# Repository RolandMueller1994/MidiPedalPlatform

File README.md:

# MidiPedalPlatform

## Introduction

This project contains a template PCB for guitar effect pedals with MIDI remote functionality. MIDI is implemented using a STM32 F030C8T6 microcontroller.
The PCB is setup to contain four 16mm potentiometers, a SPST on-off-on switch and PCB mounted jack sockets for audio connection. Further connections are the MIDI input and output, an internal switch and an external switch which are all accesible through JST connectors. A programming and debugging connector for the STLINK-V3MINIE is implemented on the PCB.

Following images show a complete pedal build based on this template.

## PCB

The PCB was developed using KiCad and a two layer setup. The KiCad project can be found in [PCB/MidiPedalPlatform](PCB/MidiPedalPlatform) whilst PCB and schematic exports are located in [PCB/Export](PCB/Export).

## Firmware

The MCU firmware is located in the [Firmware](Firmware) directory. It is implemented as STM32CubeIDE project.

The firmware handles switches and MIDI messages. By default, two switches are available: SW and ExtSW. SW is meant to be used as the default internal footswitch and must be a momentary switch. ExtSW can be used to connect an external remote switch and is by default configured to be a latching switch. This can be changed by changing:
```C
bool swLatches[NO_SWITCHES] = { false, true, true }
```
to
```C
bool swLatches[NO_SWITCHES] = { false, false, true }
```
The pedal can be switched on and off via MIDI CC commands. The channel and controller number are stored in the flash memory. Thus, a MIDI learn state and a reset state have been implemented.
To reset both parameters to their default value (channel=0, controller=20), hold the footswitch pressed (SW) while powering on or reseting the MCU till the LED starts blinking. Release the switch afterwards and the LED stops blinking. Default values will then have been written to flash.

MIDI learn is used to set any other channel and controller. This mode can be accessed by holding the footswitch pressed whilst the input jack is not connected. The LED starts blinking once MIDI learn state has been reached. In this mode, the firmware waits for a MIDI CC message and once the first one has been received, it will store the channel and controller of this message in the flash memory. MIDI learn can be aborted by pressing the footswitch again. In either case, MIDI CC received or MIDI learn aborted, the LED stops blinking.
The pedal can be switched on by sending a value greater than 63 to the configured MIDI contoller. Anything lower or equal than 63 will switch off the pedal.

The footswitch can be used in two different ways. 

- Normal activation: Toggles between on and off state
- Keeping the switch pressed whilst the pedal was off: The pedal will turn on as long you keep the switch pressed. Once release, the pedal will turn off.

## Enclosure

The PCB was design to fit into a 1590N1 enclosure. A FreeCAD project including enclosure, PCB, jacks and the switch can be found at [Enclosure/Enclosure.FCStd](Enclosure/Enclosure.FCStd). Renderings of the enclosure can be found below.
Drill templates can be found in [Enclosure/DrillTemplates](Enclosure/DrillTemplates).

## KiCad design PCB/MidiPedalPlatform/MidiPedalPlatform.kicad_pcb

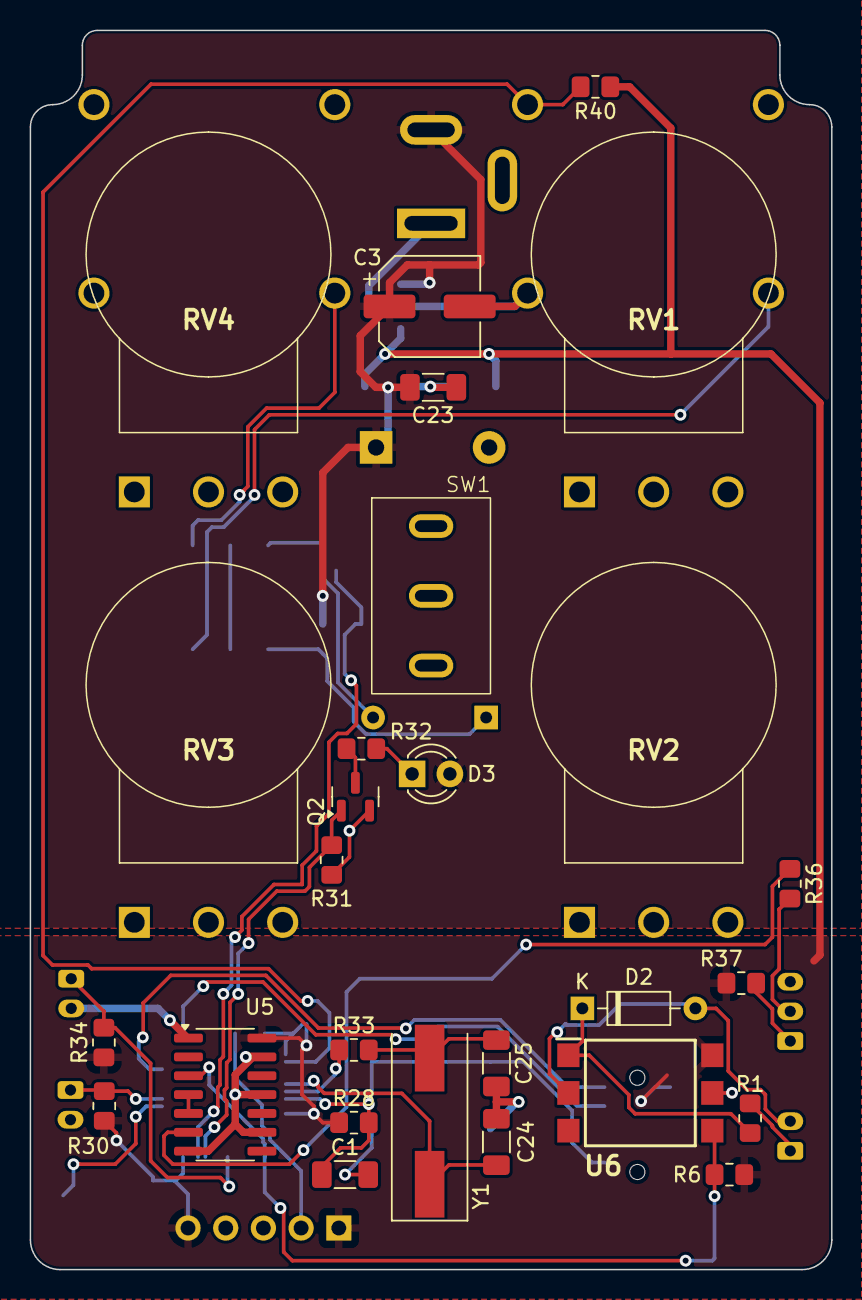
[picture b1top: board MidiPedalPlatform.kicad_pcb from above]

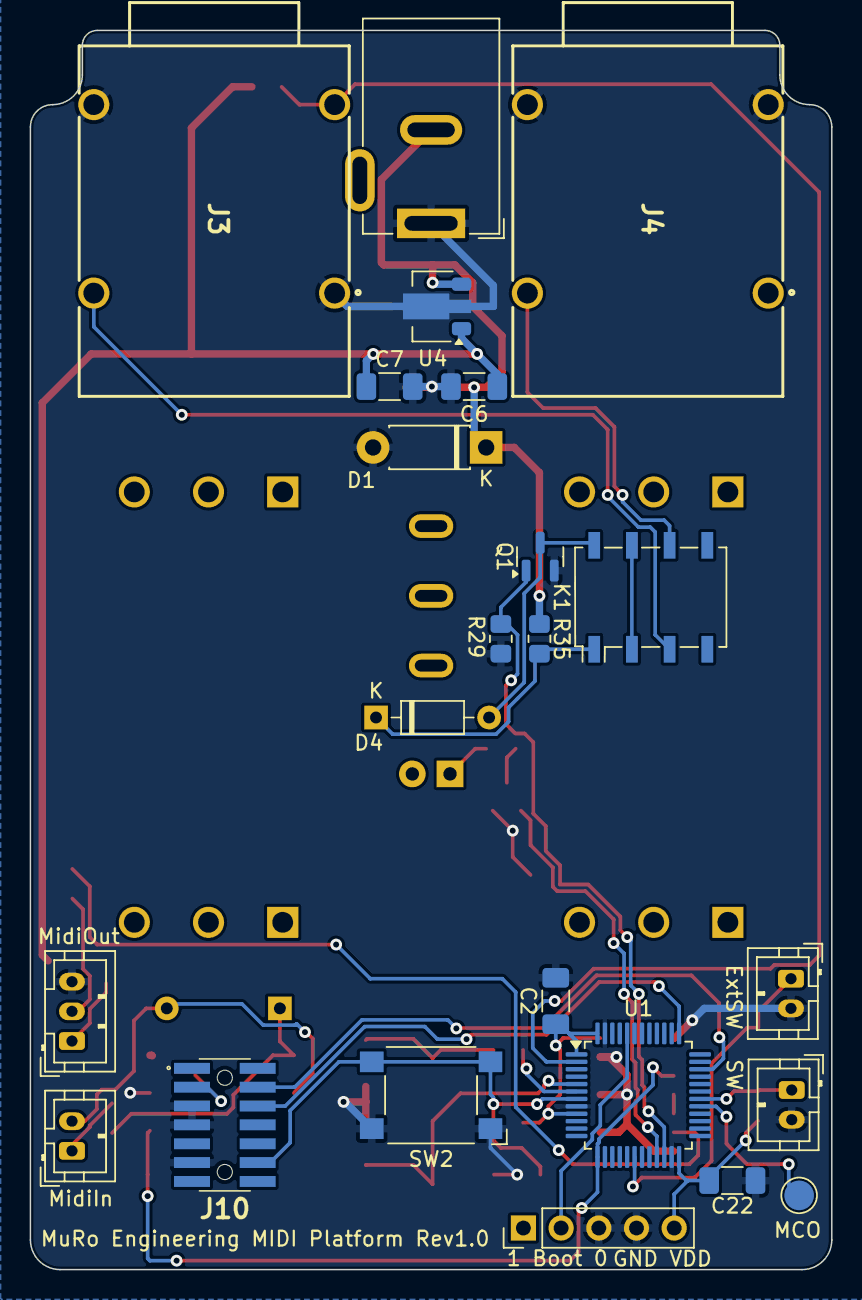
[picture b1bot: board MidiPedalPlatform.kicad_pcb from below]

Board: 2 copper layers, 54.0 x 83.5 mm, 50 parts (23 on the bottom side), 31 nets.

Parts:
C1, C2, C7, C22, C23: 100n; C_1206_3216Metric_Pad1.33x1.80mm_HandSolder
C3: 47u; CP_Elec_6.3x5.8
C6: 4u7; C_1206_3216Metric_Pad1.33x1.80mm_HandSolder
C24, C25: 16p; C_1206_3216Metric_Pad1.33x1.80mm_HandSolder
D1: 1N4001; D_DO-41_SOD81_P7.62mm_Horizontal
D2: 1N914; D_DO-35_SOD27_P7.62mm_Horizontal
D3: LED; LED_D3.0mm
D4: 1N4148; D_DO-35_SOD27_P7.62mm_Horizontal
J1: Barrel_Jack_Switch; BarrelJack_GCT_DCJ200-10-A_Horizontal
J2, J5, J8: Conn_01x02; JST_PH_B2B-PH-K_1x02_P2.00mm_Vertical
J3, J4: AudioJack2_Switch; NMJ4HCD2
J6: Conn_01x05; PinHeader_1x05_P2.54mm_Vertical
J9: Conn_01x03; JST_PH_B3B-PH-K_1x03_P2.00mm_Vertical
J10: Conn_02x07_Odd_Even; FTSH-107-XX-YYY-DV-K-A
K1: G6K-2; Relay_DPDT_Omron_G6K-2F
Q1, Q2: 2N7002; SOT-23
R1: 220; R_0805_2012Metric_Pad1.20x1.40mm_HandSolder
R6: 280; R_0805_2012Metric_Pad1.20x1.40mm_HandSolder
R28, R30, R34, R40: 10k; R_0805_2012Metric_Pad1.20x1.40mm_HandSolder
R29, R31: 100k; R_0805_2012Metric_Pad1.20x1.40mm_HandSolder
R32: 1k5; R_0805_2012Metric_Pad1.20x1.40mm_HandSolder
R33: 390; R_0805_2012Metric_Pad1.20x1.40mm_HandSolder
R35: 180; R_0805_2012Metric_Pad1.20x1.40mm_HandSolder
R36: 10; R_0805_2012Metric_Pad1.20x1.40mm_HandSolder
R37: 33; R_0805_2012Metric_Pad1.20x1.40mm_HandSolder
RV1, RV2, RV3, RV4: B100k; RV16AF_Mono
SW1: SW_SPDT; Switch_SPDT
SW2: SW_Push; SW_SPST_Omron_B3FS-100xP
TP_MCO1: TestPoint; TestPoint_Pad_D2.0mm
U1: STM32F030C8Tx; LQFP-48_7x7mm_P0.5mm
U4: L78L33_SOT89; SOT-89-3
U5: 74HC14; SO-14_3.9x8.65mm_P1.27mm
U6: H11L1; H11L1SM
Y1: 8MHz; Crystal_SMD_HC49-SD

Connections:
/ExtSW: J8.1, R34.2, U1.18 (PB0)
/InConn: J3.SN, R40.2, U1.2 (PC13)
/LED: Q2.1 (G), R31.1, U1.21 (PB10)
/MCU/OSC_IN: C24.1, U1.5 (PF0), Y1.1
/MCU/OSC_OUT: R33.1, U1.6 (PF1)
/MCU/SWCLK: J10.6, U1.37 (PA14)
/MCU/SWDIO: J10.4, U1.34 (PA13)
/MCU/boot0: J6.2, U1.44 (BOOT0)
/MCU/nrst: C1.1, J10.12, R28.2, SW2.2, U1.7 (NRST)
/MIDI_TX: R36.1, U5.6
/MidiSig: R6.1, U1.13 (PA3), U5.3, U6.4
/Relay: Q1.1 (G), R29.1, U1.22 (PB11)
/SW: J5.1, R30.2, U1.30 (PA9)
/VDD: C3.1, C23.1, D1.1 (K), D3.2 (A), J1.2, R35.1, U4.3 (IN)
/VDD3V3: C2.1, C6.1, C7.1, C22.1, J6.1, J6.5, J10.3, R6.2, R28.1, R30.1, R34.1, R37.1, R40.1, U1.1 (VDD), U1.9 (VDDA), U1.24 (VDD), U1.48 (VDD), U4.1 (OUT), U5.14 (VCC), U6.6
GND: C1.2, C2.2, C3.2, C6.2, C7.2, C22.2, C23.2, C24.2, C25.2, D1.2 (A), J1.1, J3.S, J3.TN, J4.S, J4.SN, J5.2, J6.3, J6.4, J8.2, J9.3, J10.5, J10.7, J10.11, Q1.2 (S), Q2.2 (S), R29.2, R31.2, SW2.1, U1.8 (VSSA), U1.23 (VSS), U1.47 (VSS), U4.2 (GND), U5.1, U5.7 (GND), U5.9, U5.11, U5.13, U6.5
unnamed: C25.1, R33.2, Y1.2
unnamed: D2.2 (A), J2.2, U6.2
unnamed: D2.1 (K), R1.2, U6.1
unnamed: D3.1 (K), R32.1
unnamed: D4.2 (A), K1.8, Q1.3 (D)
unnamed: D4.1 (K), K1.1, R35.2
unnamed: J2.1, R1.1
unnamed: J3.T, K1.3
unnamed: J4.T, K1.6
unnamed: J9.1, R37.2
unnamed: J9.2, R36.2
unnamed: K1.2, K1.7
unnamed: Q2.3 (D), R32.2
unnamed: TP_MCO1.1, U1.29 (PA8)
unnamed: U5.4, U5.5

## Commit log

2025-02-16 Initial commit including license and gitignore
2025-02-16 Imported firmware with basic hardware configuration. This is a clean STM32 project for the target microcontroller including the IO configuration.
2025-02-16 First version of switch debouncing.
    In this version, momentary switches are properly debounced and their state is traced for falling edge (active low) operation.
    Dual edge debouncing and latching switch operation yet to be implemented.
2025-02-16 Added push and release edge detection and debouncing.
    With this change, lateched switches can be used to trigger the effectOn state by tracking the edges.
2025-02-16 Added long press functionality for momentary switches.
    This feature detects momentary switches been pressed for longer than a certain time (LONG_DELAY). This can be used to temporarily activate the effect as long as the switched is pressed. After release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
2025-02-16 First midi implemenation. This version only works with CC messages.
2025-02-16 Switched UART to UARTEx functions to use ReceiveToIdle functions.
    MIDI packages are either two or three bytes long. Thus, e.g. PC messages would not fill the whole RX buffer and therefore mess up the package sequence.
    ReceiveToIdle executes the callback once the length is reached or no further data is transfered (idle). Therefore, the interupts are called after each MIDI package no matter the length.
2025-02-16 Added MIDI learn functionality and reset.
    If the main switch is pressed at power on, default MIDI channel 1 and controller 20 are stored.
    If the main switch is pressed during operation and the input jack is not connected, MIDI learn is started. In this case, the device waits till it receives the first CC message. The channel and contro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
2025-02-18 Addition of periodic UART overrun check.
    UART gets into overrun condition once it receives data and the previous data has not been consumed by the application yet. In this case the ORE bit (bit 3) in the ISR register is set to 1 which disab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
    This can broken interrupts after midi learn and write to flash. During write to flash, the interrupts and therefore the data are not consumed which leads to broken interupts.
2025-02-18 Changes: - Default midi channel set to 0 - Wait at reset till switch is released. Before we would get into midi learn if the switch is not release quickly enough. - Reset loop count in main once midi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
2025-02-18 Reduced midi ring buffer size to 32 and each transfer in it buffer to the minimum of 3 bytes. Comments for documentation.
2025-02-22 Added FreeCAD project with import Hammond 1590N1 enclosure
2025-02-22 Added PCB and the required components.
    Layout and schematic are matching. There are 15 warnings DRC warnings expected from silkscreen being clipped by other components or PCB edge.
2025-02-22 Removed bom
2025-02-22 Removed backup files
2025-02-22 Enclosure version with cutouts for parts. Midi input and output jacks still missing.
2025-02-23 Added images and exports. Enclosure now contains 3.5mm jacks for MIDI in and out
2025-02-23 Fixed typos
2025-12-30 Added firmware project files such that CubeIDE recognizes the project
